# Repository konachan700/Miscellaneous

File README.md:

# Miscellaneous

В этой папке я складываю всяческий хлам, дабы не засорять всякой мелочевкой основной список реп. Во многих папках есть свои ридми с описаниями.

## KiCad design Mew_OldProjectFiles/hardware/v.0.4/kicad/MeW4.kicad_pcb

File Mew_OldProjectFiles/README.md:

### Mew
Hardware password manager.

### Для русскоязычных пользователей
[Страничка в вики на русском](https://github.com/konachan700/Mew/wiki/%D0%9E%D0%BF%D0%B8%D1%81%D0%B0%D0%BD%D0%B8%D0%B5-%D1%83%D1%81%D1%82%D1%80%D0%BE%D0%B9%D1%81%D1%82%D0%B2%D0%B0-%D0%BD%D0%B0-%D1%80%D1%83%D1%81%D1%81%D0%BA%D0%BE%D0%BC)

### What is it? 
It's a small USB devise for safety passwords storing. The device not require any driver on most popular desktop OSes, and compatable with Android OS. You do not need any special skills to use Mew.

### Why Opensource? Are not you afraid that Chinese manufacturers will steal the idea?
1. The closed-source device cannot be a secure, because it may contain a backdoor for the manufacturer, for hacker 
in the sales chain or for a government. Only open source device can be a trusted. <br>
2. No. I develop the device first of all for myself, for study STM32. Anybody can make Mew, but I do not give a guarantee that I will continue to support the device.

### Where I can buy Mew?
Currently nowhere. You can make Mew yourself. In future time, may be, I will selling Mew in a project website.

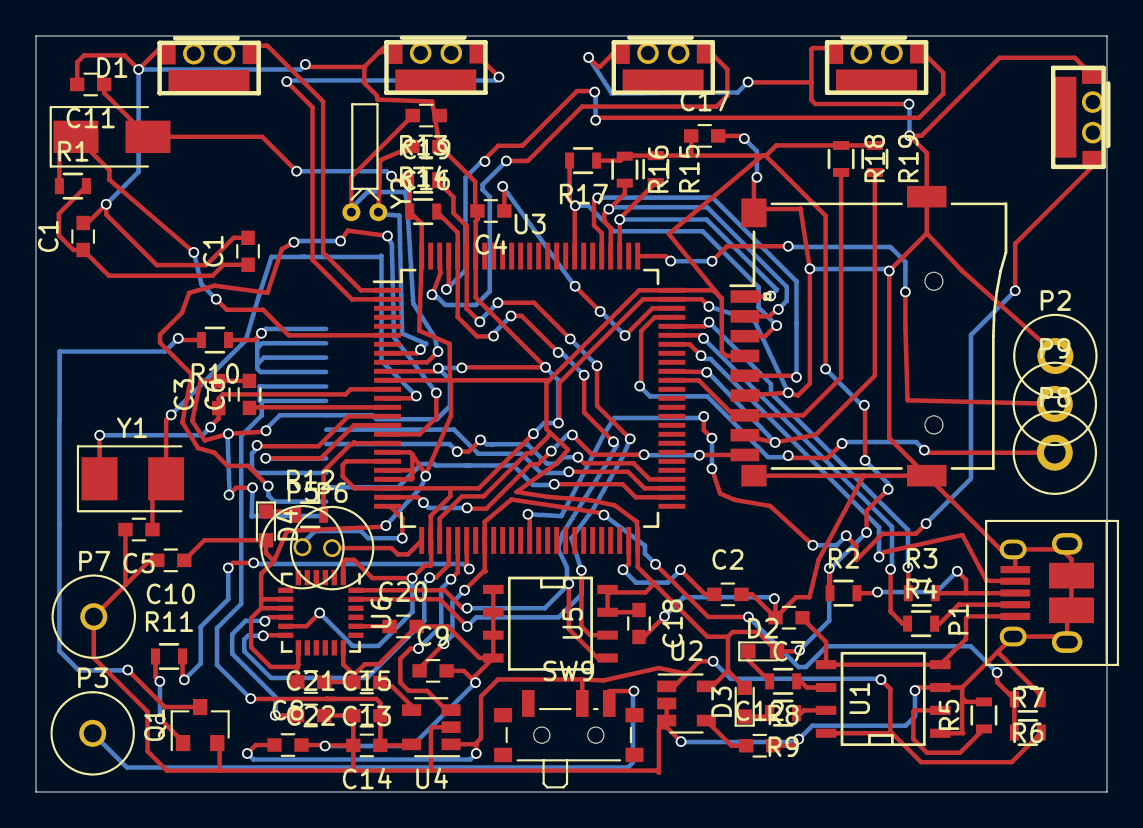
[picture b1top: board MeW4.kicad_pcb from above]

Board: 2 copper layers, 59.5 x 42.0 mm, 71 parts (1 on the bottom side), 61 nets.

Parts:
C1, C1#2: 0.1F; C_0603
C2, C4: 2.2uF; C_0603
C3, C5, C16, C19: 22; C_0603
C6, C11, C14, C21: 0.1uF; C_0603
C7, C8: 10uF; C_0603
C9: 33; C_0603
C10: C; C_0603
C12, C13, C15, C17, C22: 0.01uF; C_0603
C18: 10nF; C_0603
C20: 2.2nF; C_0603
CON1: uSD_Card; Conn_uSDcard
D1: 1n5819; D_SMA_Standard
D2: RED; LED_0603
D3: GREEN; LED_0603
D4: LED; LED_0603
P1: USB_OTG; USB_Micro-B_10103594-0001LF
P2: BAT-; 1pin
P3: BAT+; 1pin
P4: CONN_01X18; DISP1
P5: TX2; 1pin
P6: RX2; 1pin
P7: GND; 1pin
P8: SWDIO; 1pin
P9: SWDCLK; 1pin
Q1: 2N7002; SOT-23
R1, R11: 100; R_0603
R2: 1.5k; R_0603
R3, R4: 22; R_0603
R5: 10k; R_0603
R6, R7: 100k; R_0603
R8, R9, R12: 1k; R_0603
R10: 0; R_0603
R13, R14: 1k5; R_0603
R15, R16, R17, R18, R19: 33k; R_0603
SW1: BACK; SMDBTN1
SW2: ENTER; SMDBTN1
SW3: UP; SMDBTN1
SW4: DOWN; SMDBTN1
SW5: USER4; SMDBTN1
SW9: SWITCH_INV; SW_SPDT_PCM12
U1: TPS4056; SOIC-8-N
U2: TPS79133DBVR; SOT-23-5
U3: STM32F217VETx; LQFP-100_14x14mm_Pitch0.5mm
U4: TPS79318-EP; SOT-23-5
U5: 24C16; SOIC-8-N
U6: MPU-6050; QFN-24_4x4mm_Pitch0.5mm
Y1: 8MHz; Crystal_SMD_5032-2pin_5.0x3.2mm
Y2: 32k; Crystal_DS10_d1.0mm_l4.3mm_Horizontal

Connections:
+3V3: C10.1, C11.1, C17.1, C18.1, C22.2, CON1.4, D1.2, D2.2, D3.2, D4.2, R2.1, R13.1, R14.1, R15.1, R16.1, R17.1, R18.1, R19.1, U2.5, U3.11, U3.19, U3.21, U3.22, U3.28, U3.50, U3.75, U3.100, U5.7, U5.8, U6.8, U6.9, U6.13
/ADC0: C9.1, R6.2, R7.1, U3.33
/B1: SW1.2, U3.97
/B2: SW2.2, U3.98
/B3: SW3.2, U3.1
/B8: SW5.2, U3.38
/CD: CON1.9, U3.24
/CHRG1: R8.1, U1.6
/CHRG2: R9.1, U1.7
/DISP_CLK: P4.3, U3.52
/DISP_CS: P4.5, U3.16
/DISP_D/C: P4.4, U3.15
/DISP_EN: U3.30, U4.3
/DISP_MISO: P4.7, U3.53
/DISP_MOSI: P4.6, U3.54
/DISP_PWM: Q1.1, R11.1
/DISP_RES: P4.2, U3.17
/MPU_INT: U3.29, U6.12
/SDIO_CLK: CON1.5, U3.80
/SDIO_CMD: CON1.3, R17.2, U3.83
/SDIO_D0: CON1.7, R18.2, U3.65
/SDIO_D1: CON1.8, R19.2, U3.66
/SDIO_D2: CON1.1, R15.2, U3.78
/SDIO_D3: CON1.2, R16.2, U3.79
/USB-DM: R4.1, U3.70
/USB-DP: R3.1, U3.71
/USB-ID: P1.4, U3.69
/VBAT: C8.1, R7.2, SW9.2, U1.8, U2.1, U4.1
/VBAT_RTC: D1.1, R1.1, U3.6
/VCC5: C7.1, P1.1, U1.4, U1.5
/i2c_SCL: R13.2, U3.95, U5.6, U6.23
/i2c_SDA: R14.2, U3.96, U5.5, U6.24
GND: C1.2, C1#2.2, C2.2, C3.2, C4.2, C5.2, C6.2, C7.2, C8.2, C9.2, C10.2, C11.2, C12.2, C13.2, C14.2, C15.1, C16.1, C17.2, C18.2, C19.1, C20.2, C21.2, C22.1, CON1.6, P1.5, P1.6, P2.1, P4.1, P4.8, P7.1, Q1.2, R5.2, R6.1, SW1.1, SW2.1, SW3.1, SW4.1, SW5.1, U1.1, U1.3, U2.2, U2.3, U3.10, U3.20, U3.23, U3.27, U3.74, U3.94, U4.2, U5.1, U5.2, U5.3, U5.4, U6.1, U6.11, U6.18
unnamed: C1.1, C1#2.1, R1.2
unnamed: C2.1, U3.49
unnamed: C3.1, U3.12, Y1.1
unnamed: C4.1, U3.73
unnamed: C5.1, U3.13, Y1.2
unnamed: C6.1, U3.14
unnamed: C12.1, U2.4
unnamed: C13.1, U4.4
unnamed: C14.1, C15.2, P4.9, P4.10, U4.5
unnamed: C16.2, U3.8, Y2.1
unnamed: C19.2, U3.9, Y2.2
unnamed: C20.1, U6.20
unnamed: C21.1, U6.10
unnamed: D2.1, R8.2
unnamed: D3.1, R9.2
unnamed: D4.1, R12.1
unnamed: P1.2, R4.2
unnamed: P1.3, R2.2, R3.2
unnamed: P3.1, SW9.3
unnamed: P4.11, P4.12, P4.13, P4.14, R10.1
unnamed: P5.1, U3.25
unnamed: P6.1, U3.26
unnamed: P8.1, U3.72
unnamed: P9.1, U3.76
unnamed: Q1.3, R10.2
unnamed: R5.1, U1.2
unnamed: R11.2, U3.31
unnamed: R12.2, U3.18

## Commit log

2017-09-05 inital commit
2017-09-05 add some code
